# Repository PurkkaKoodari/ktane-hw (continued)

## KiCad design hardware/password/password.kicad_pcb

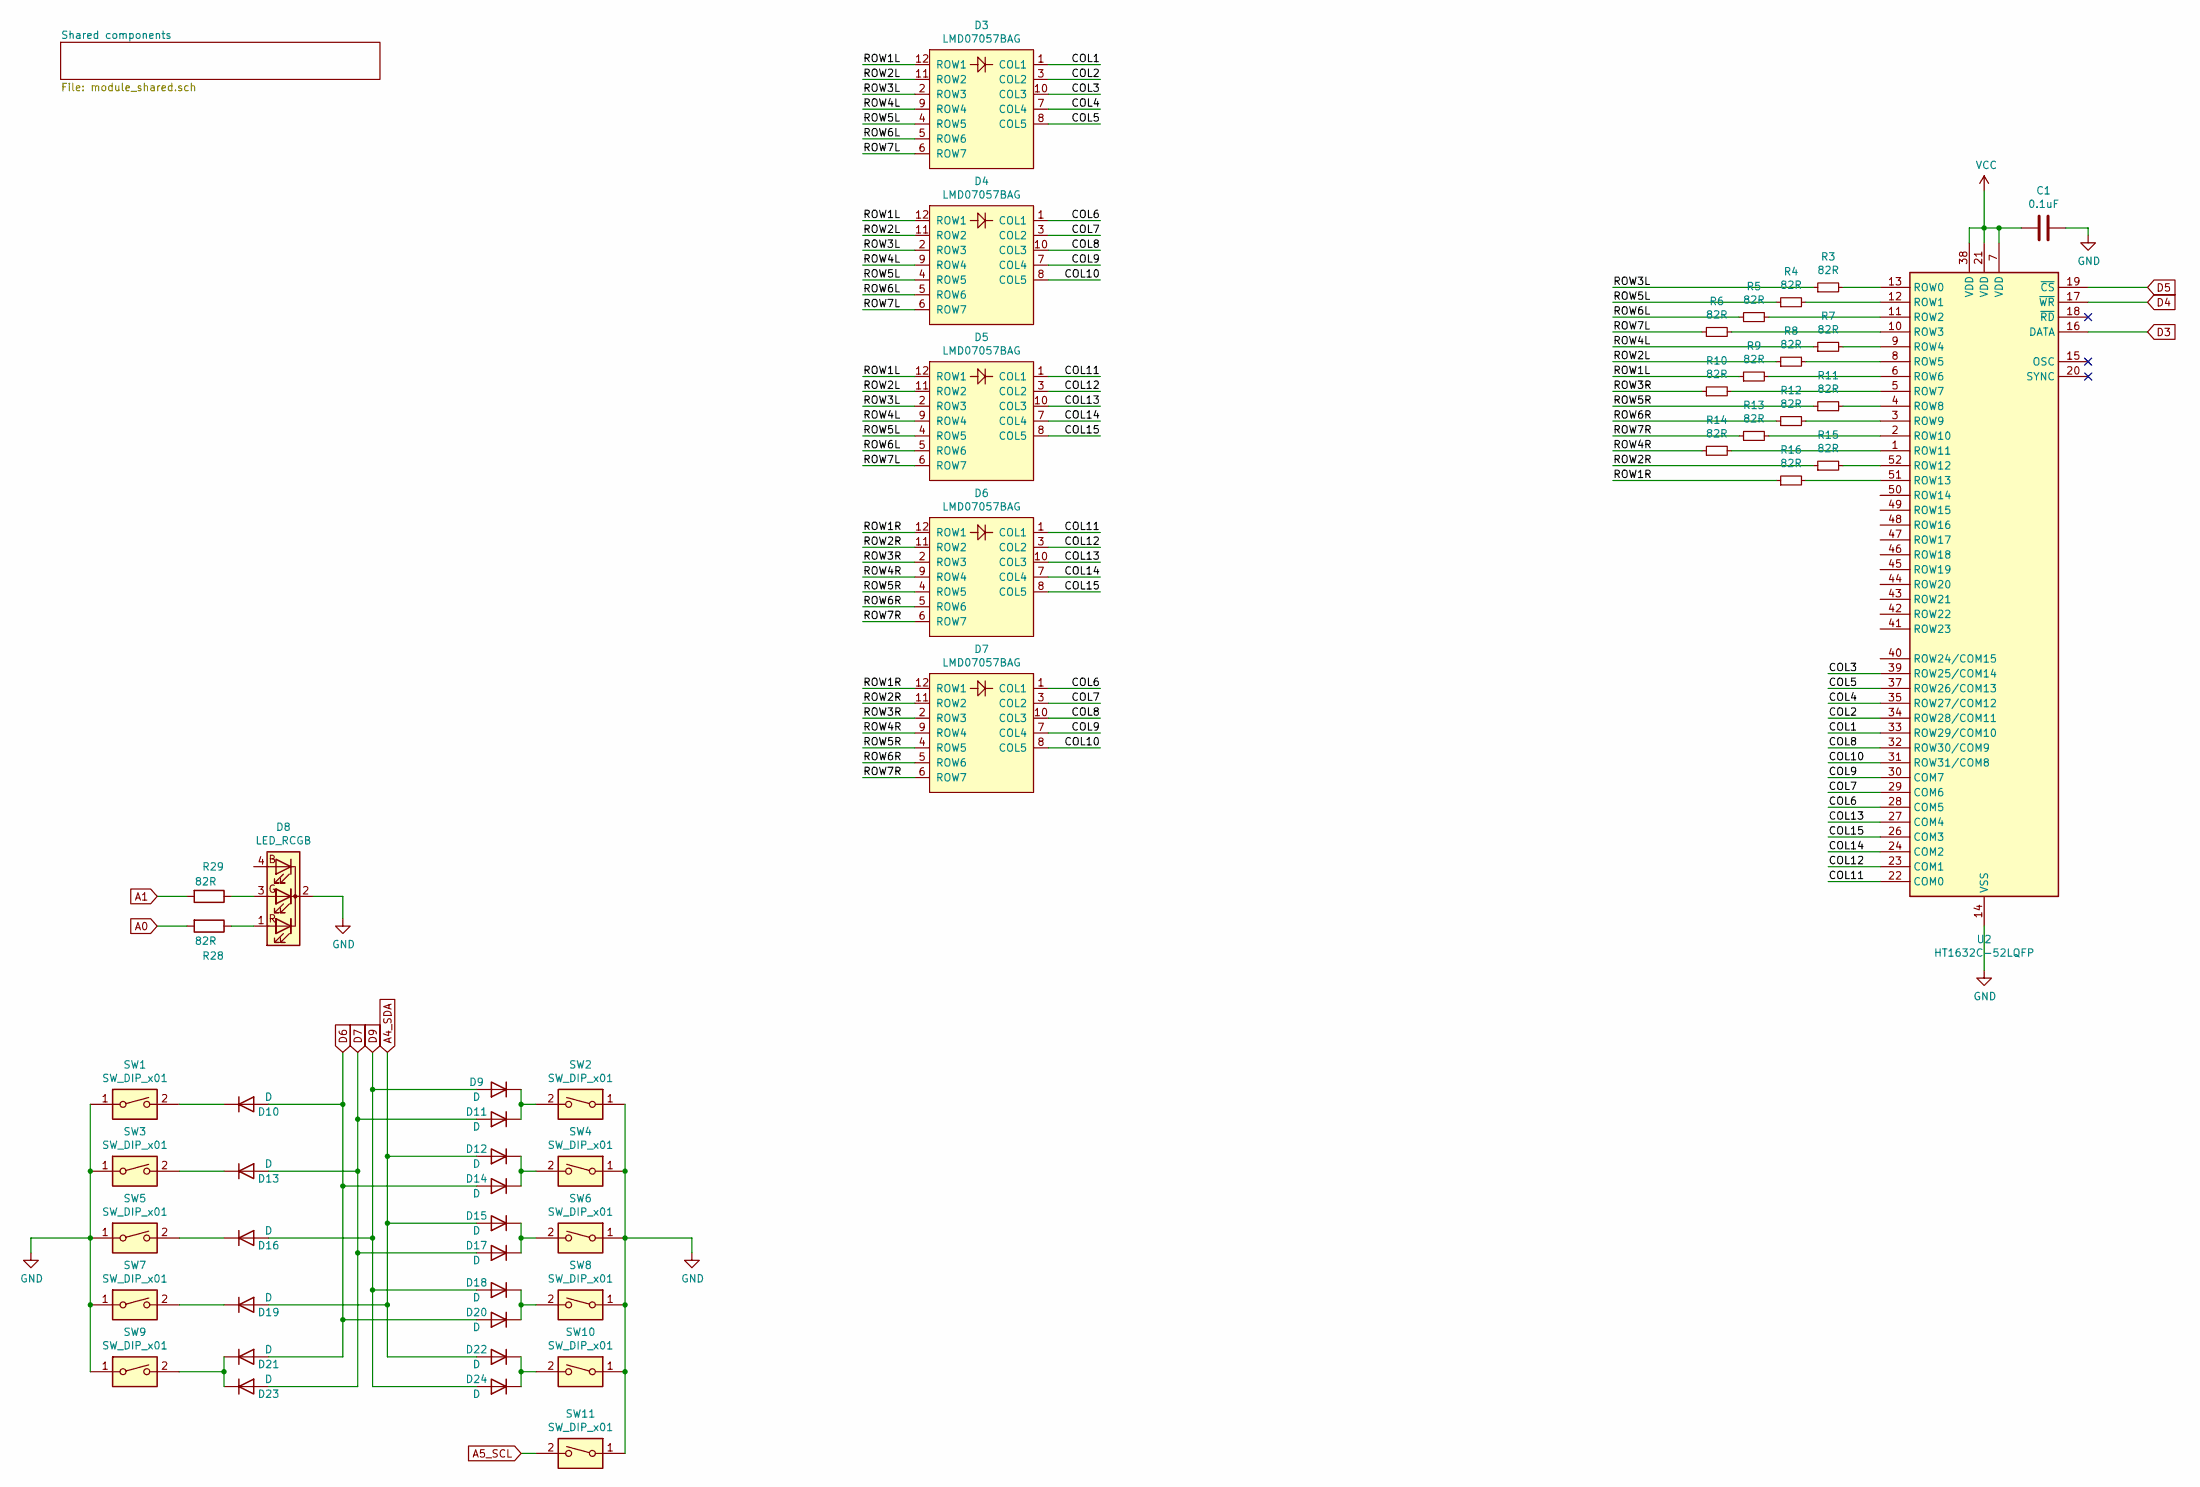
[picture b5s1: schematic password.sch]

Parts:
C1: 0.1uF; C_0603_1608Metric_Pad1.05x0.95mm_HandSolder
D3, D4, D5, D6, D7: LMD07057BAG
D8: LED_RCGB; LED_D5.0mm-4_RGB_Wide_Pins
D9, D10, D11, D12, D13, D14, D15, D16, D17, D18, D19, D20, D21, D22, D23, D24: D; D_0805_2012Metric_Pad1.15x1.40mm_HandSolder
R3, R4, R5, R6, R7, R8, R9, R10, R11, R12, R13, R14, R15, R16, R28, R29: 82R; R_0603_1608Metric_Pad0.98x0.95mm_HandSolder
SW1, SW2, SW3, SW4, SW5, SW6, SW7, SW8, SW9, SW10, SW11: SW_DIP_x01; SW_Push_1P1T_NO_6x6mm_H9.5mm
U2: HT1632C-52LQFP; LQFP-52_14x14mm_P1mm

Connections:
/COL1: D3.1 (COL1), U2.33 (ROW29/COM10)
/COL2: D3.3 (COL2), U2.34 (ROW28/COM11)
/COL3: D3.10 (COL3), U2.39 (ROW25/COM14)
/COL4: D3.7 (COL4), U2.35 (ROW27/COM12)
/COL5: D3.8 (COL5), U2.37 (ROW26/COM13)
/COL6: D4.1 (COL1), D7.1 (COL1), U2.28 (COM5)
/COL7: D4.3 (COL2), D7.3 (COL2), U2.29 (COM6)
/COL8: D4.10 (COL3), D7.10 (COL3), U2.32 (ROW30/COM9)
/COL9: D4.7 (COL4), D7.7 (COL4), U2.30 (COM7)
/COL10: D4.8 (COL5), D7.8 (COL5), U2.31 (ROW31/COM8)
/COL11: D5.1 (COL1), D6.1 (COL1), U2.22 (COM0)
/COL12: D5.3 (COL2), D6.3 (COL2), U2.23 (COM1)
/COL13: D5.10 (COL3), D6.10 (COL3), U2.27 (COM4)
/COL14: D5.7 (COL4), D6.7 (COL4), U2.24 (COM2)
/COL15: D5.8 (COL5), D6.8 (COL5), U2.26 (COM3)
/ROW1L: D3.12 (ROW1), D4.12 (ROW1), D5.12 (ROW1), R9.1
/ROW1R: D6.12 (ROW1), D7.12 (ROW1), R16.1
/ROW2L: D3.11 (ROW2), D4.11 (ROW2), D5.11 (ROW2), R8.1
/ROW2R: D6.11 (ROW2), D7.11 (ROW2), R15.1
/ROW3L: D3.2 (ROW3), D4.2 (ROW3), D5.2 (ROW3), R3.1
/ROW3R: D6.2 (ROW3), D7.2 (ROW3), R10.1
/ROW4L: D3.9 (ROW4), D4.9 (ROW4), D5.9 (ROW4), R7.1
/ROW4R: D6.9 (ROW4), D7.9 (ROW4), R14.1
/ROW5L: D3.4 (ROW5), D4.4 (ROW5), D5.4 (ROW5), R4.1
/ROW5R: D6.4 (ROW5), D7.4 (ROW5), R11.1
/ROW6L: D3.5 (ROW6), D4.5 (ROW6), D5.5 (ROW6), R5.1
/ROW6R: D6.5 (ROW6), D7.5 (ROW6), R12.1
/ROW7L: D3.6 (ROW7), D4.6 (ROW7), D5.6 (ROW7), R6.1
/ROW7R: D6.6 (ROW7), D7.6 (ROW7), R13.1
A0: R28.2; also elsewhere on the board
A1: R29.2; also elsewhere on the board
A4_SDA: D12.2 (A), D15.2 (A), D19.2 (A), D22.2 (A); also elsewhere on the board
A5_SCL: SW11.2; also elsewhere on the board
D3: U2.16 (DATA); also elsewhere on the board
D4: U2.17 (~WR); also elsewhere on the board
D5: U2.19 (~CS); also elsewhere on the board
D6: D10.2 (A), D14.2 (A), D20.2 (A), D21.2 (A); also elsewhere on the board
D7: D11.2 (A), D13.2 (A), D17.2 (A), D23.2 (A); also elsewhere on the board
D9: D9.2 (A), D16.2 (A), D18.2 (A), D24.2 (A); also elsewhere on the board
GND: C1.1, D8.2 (K), SW1.1, SW2.1, SW3.1, SW4.1, SW5.1, SW6.1, SW7.1, SW8.1, SW9.1, SW10.1, SW11.1, U2.14 (VSS), U2.25 (VSS), U2.36 (VSS); also elsewhere on the board
unnamed: D8.1 (RA), R28.1
unnamed: D8.3 (GA), R29.1
unnamed: D10.1 (K), SW1.2
unnamed: D9.1 (K), D11.1 (K), SW2.2
unnamed: D12.1 (K), D14.1 (K), SW4.2
unnamed: D13.1 (K), SW3.2
unnamed: D15.1 (K), D17.1 (K), SW6.2
unnamed: D16.1 (K), SW5.2
unnamed: D18.1 (K), D20.1 (K), SW8.2
unnamed: D19.1 (K), SW7.2
unnamed: D21.1 (K), D23.1 (K), SW9.2
unnamed: D22.1 (K), D24.1 (K), SW10.2
unnamed: R3.2, U2.13 (ROW0)
unnamed: R4.2, U2.12 (ROW1)
unnamed: R5.2, U2.11 (ROW2)
unnamed: R6.2, U2.10 (ROW3)
unnamed: R7.2, U2.9 (ROW4)
unnamed: R8.2, U2.8 (ROW5)
unnamed: R9.2, U2.6 (ROW6)
unnamed: R10.2, U2.5 (ROW7)
unnamed: R11.2, U2.4 (ROW8)
unnamed: R12.2, U2.3 (ROW9)
unnamed: R13.2, U2.2 (ROW10)
unnamed: R14.2, U2.1 (ROW11)
unnamed: R15.2, U2.52 (ROW12)
unnamed: R16.2, U2.51 (ROW13)
VCC: C1.2, U2.7 (VDD), U2.21 (VDD), U2.38 (VDD); also elsewhere on the board

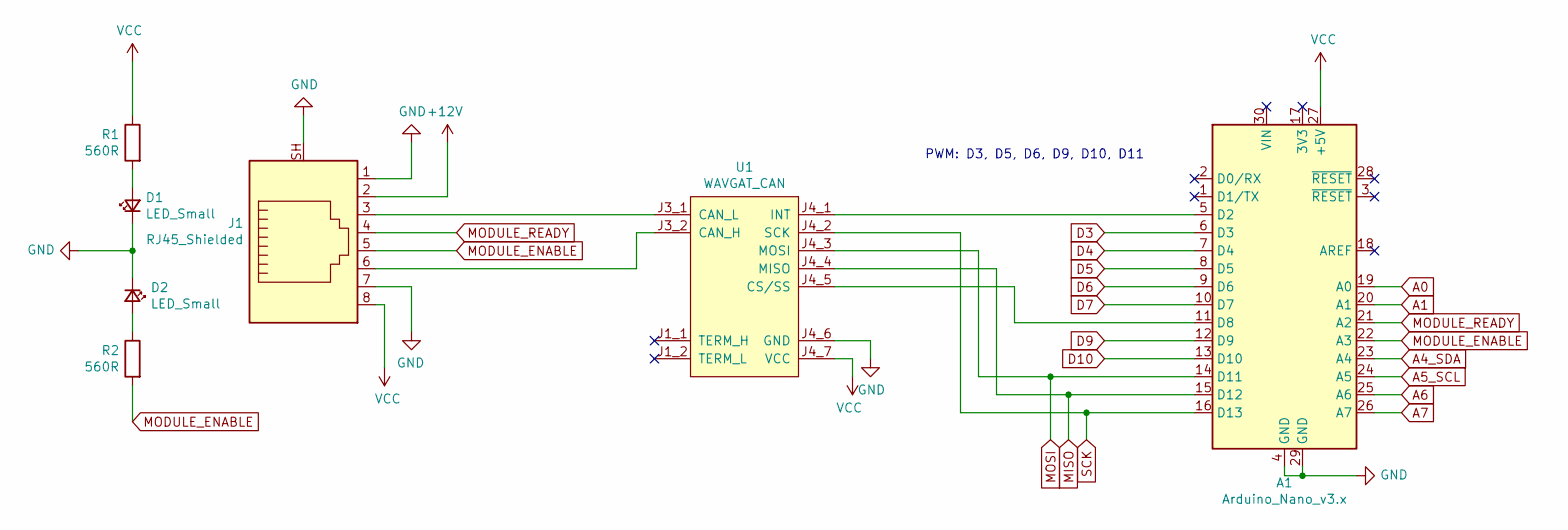
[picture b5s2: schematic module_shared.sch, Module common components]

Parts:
A1: Arduino_Nano_v3.x; Arduino_Nano
D1, D2: LED_Small; LED_D3.0mm
J1: RJ45_Shielded; RJ45_5224
R1, R2: 560R; R_0603_1608Metric_Pad0.98x0.95mm_HandSolder
U1: WAVGAT_CAN

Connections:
+12V: J1.2
A0: A1.19 (A0); also elsewhere on the board
A1: A1.20 (A1); also elsewhere on the board
A4_SDA: A1.23 (A4); also elsewhere on the board
A5_SCL: A1.24 (A5); also elsewhere on the board
A6: A1.25 (A6)
A7: A1.26 (A7)
D3: A1.6 (D3); also elsewhere on the board
D4: A1.7 (D4); also elsewhere on the board
D5: A1.8 (D5); also elsewhere on the board
D6: A1.9 (D6); also elsewhere on the board
D7: A1.10 (D7); also elsewhere on the board
D9: A1.12 (D9); also elsewhere on the board
D10: A1.13 (D10)
GND: A1.4 (GND), A1.29 (GND), D1.1 (K), D2.1 (K), J1.1, J1.7, J1.SH, U1.J4_6 (GND); also elsewhere on the board
MISO: A1.15 (D12), U1.J4_4 (MISO)
MODULE_ENABLE: A1.22 (A3), J1.5, R2.2
MODULE_READY: A1.21 (A2), J1.4
MOSI: A1.14 (D11), U1.J4_3 (MOSI)
unnamed: A1.5 (D2), U1.J4_1 (INT)
unnamed: A1.11 (D8), U1.J4_5 (CS/SS)
unnamed: D1.2 (A), R1.2
unnamed: D2.2 (A), R2.1
unnamed: J1.3, U1.J3_1 (CAN_L)
unnamed: J1.6, U1.J3_2 (CAN_H)
SCK: A1.16 (D13), U1.J4_2 (SCK)
VCC: A1.27 (+5V), J1.8, R1.1, U1.J4_7 (VCC); also elsewhere on the board

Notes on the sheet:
PWM: D3, D5, D6, D9, D10, D11

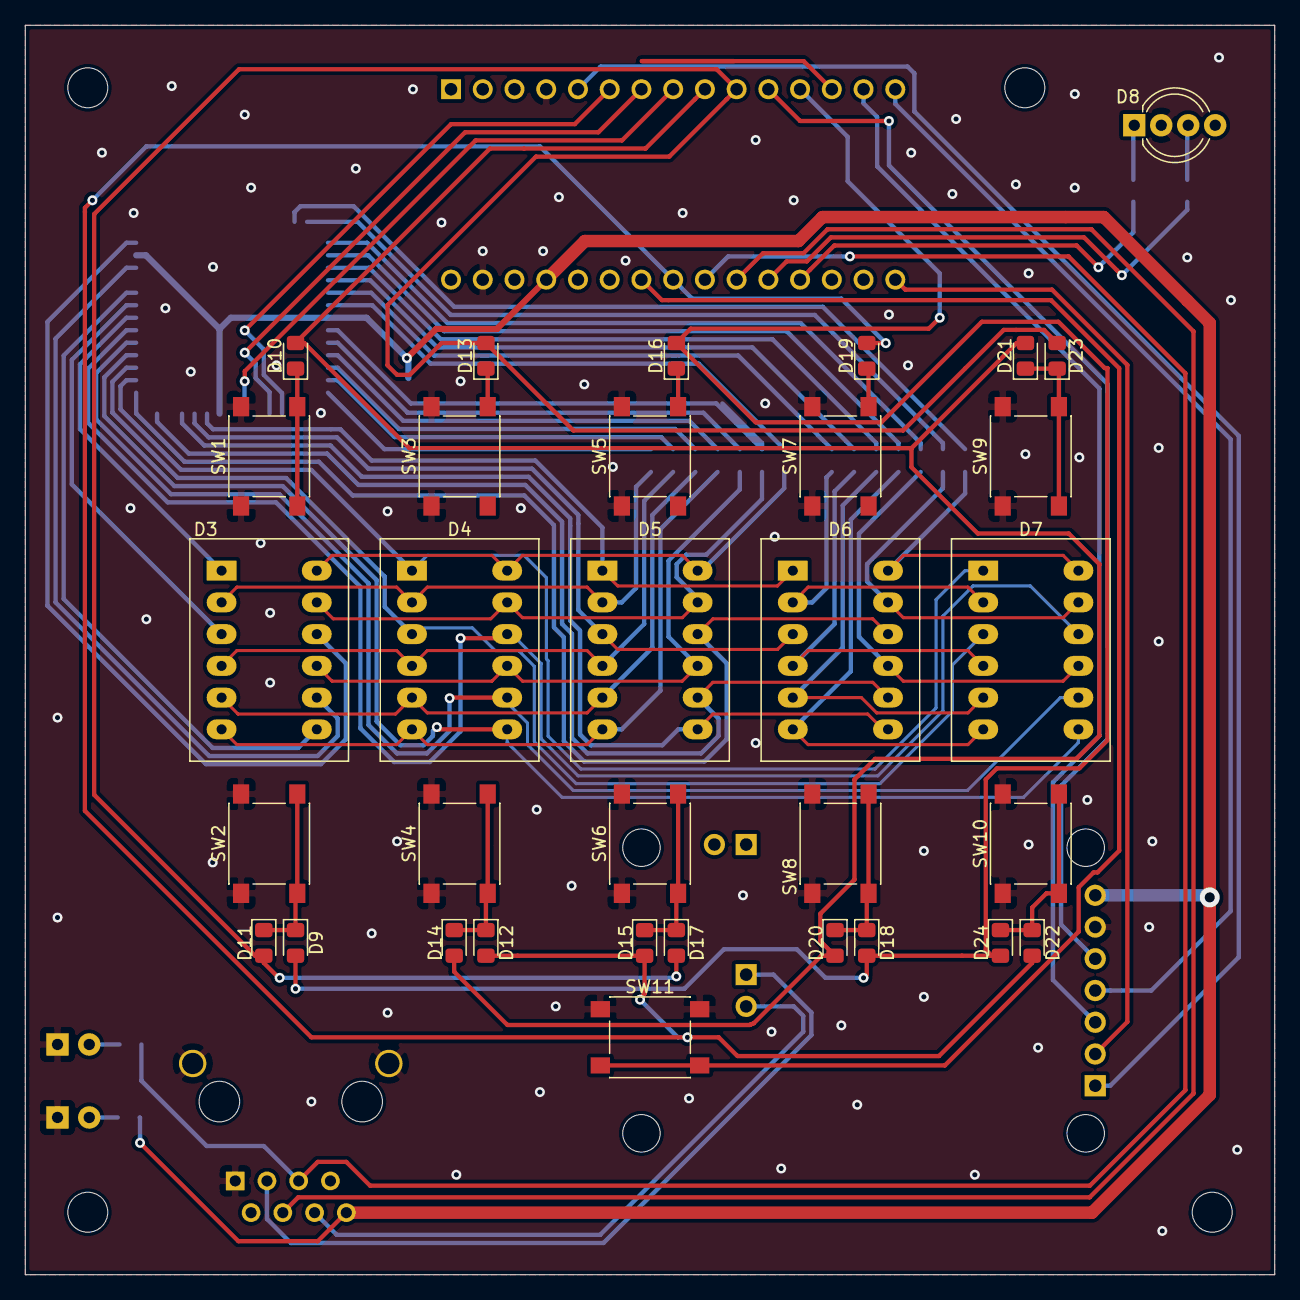
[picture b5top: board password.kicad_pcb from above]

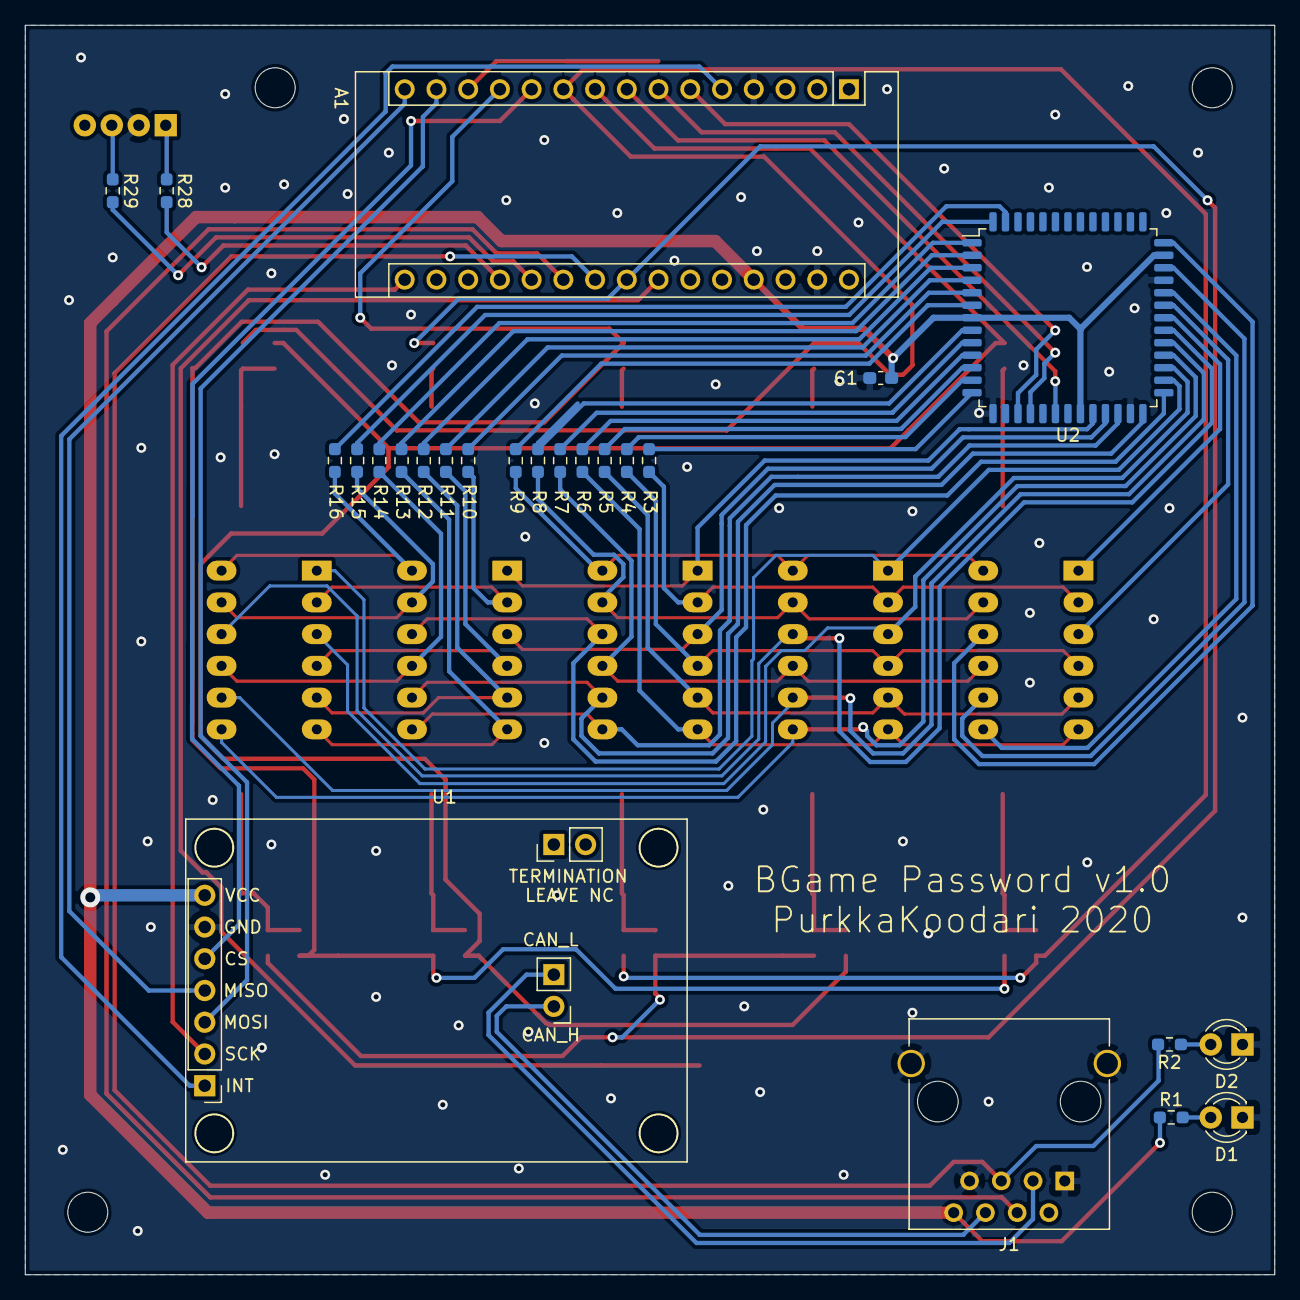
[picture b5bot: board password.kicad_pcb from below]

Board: 2 copper layers, 100.0 x 100.0 mm, 58 parts (25 on the bottom side), 78 nets.

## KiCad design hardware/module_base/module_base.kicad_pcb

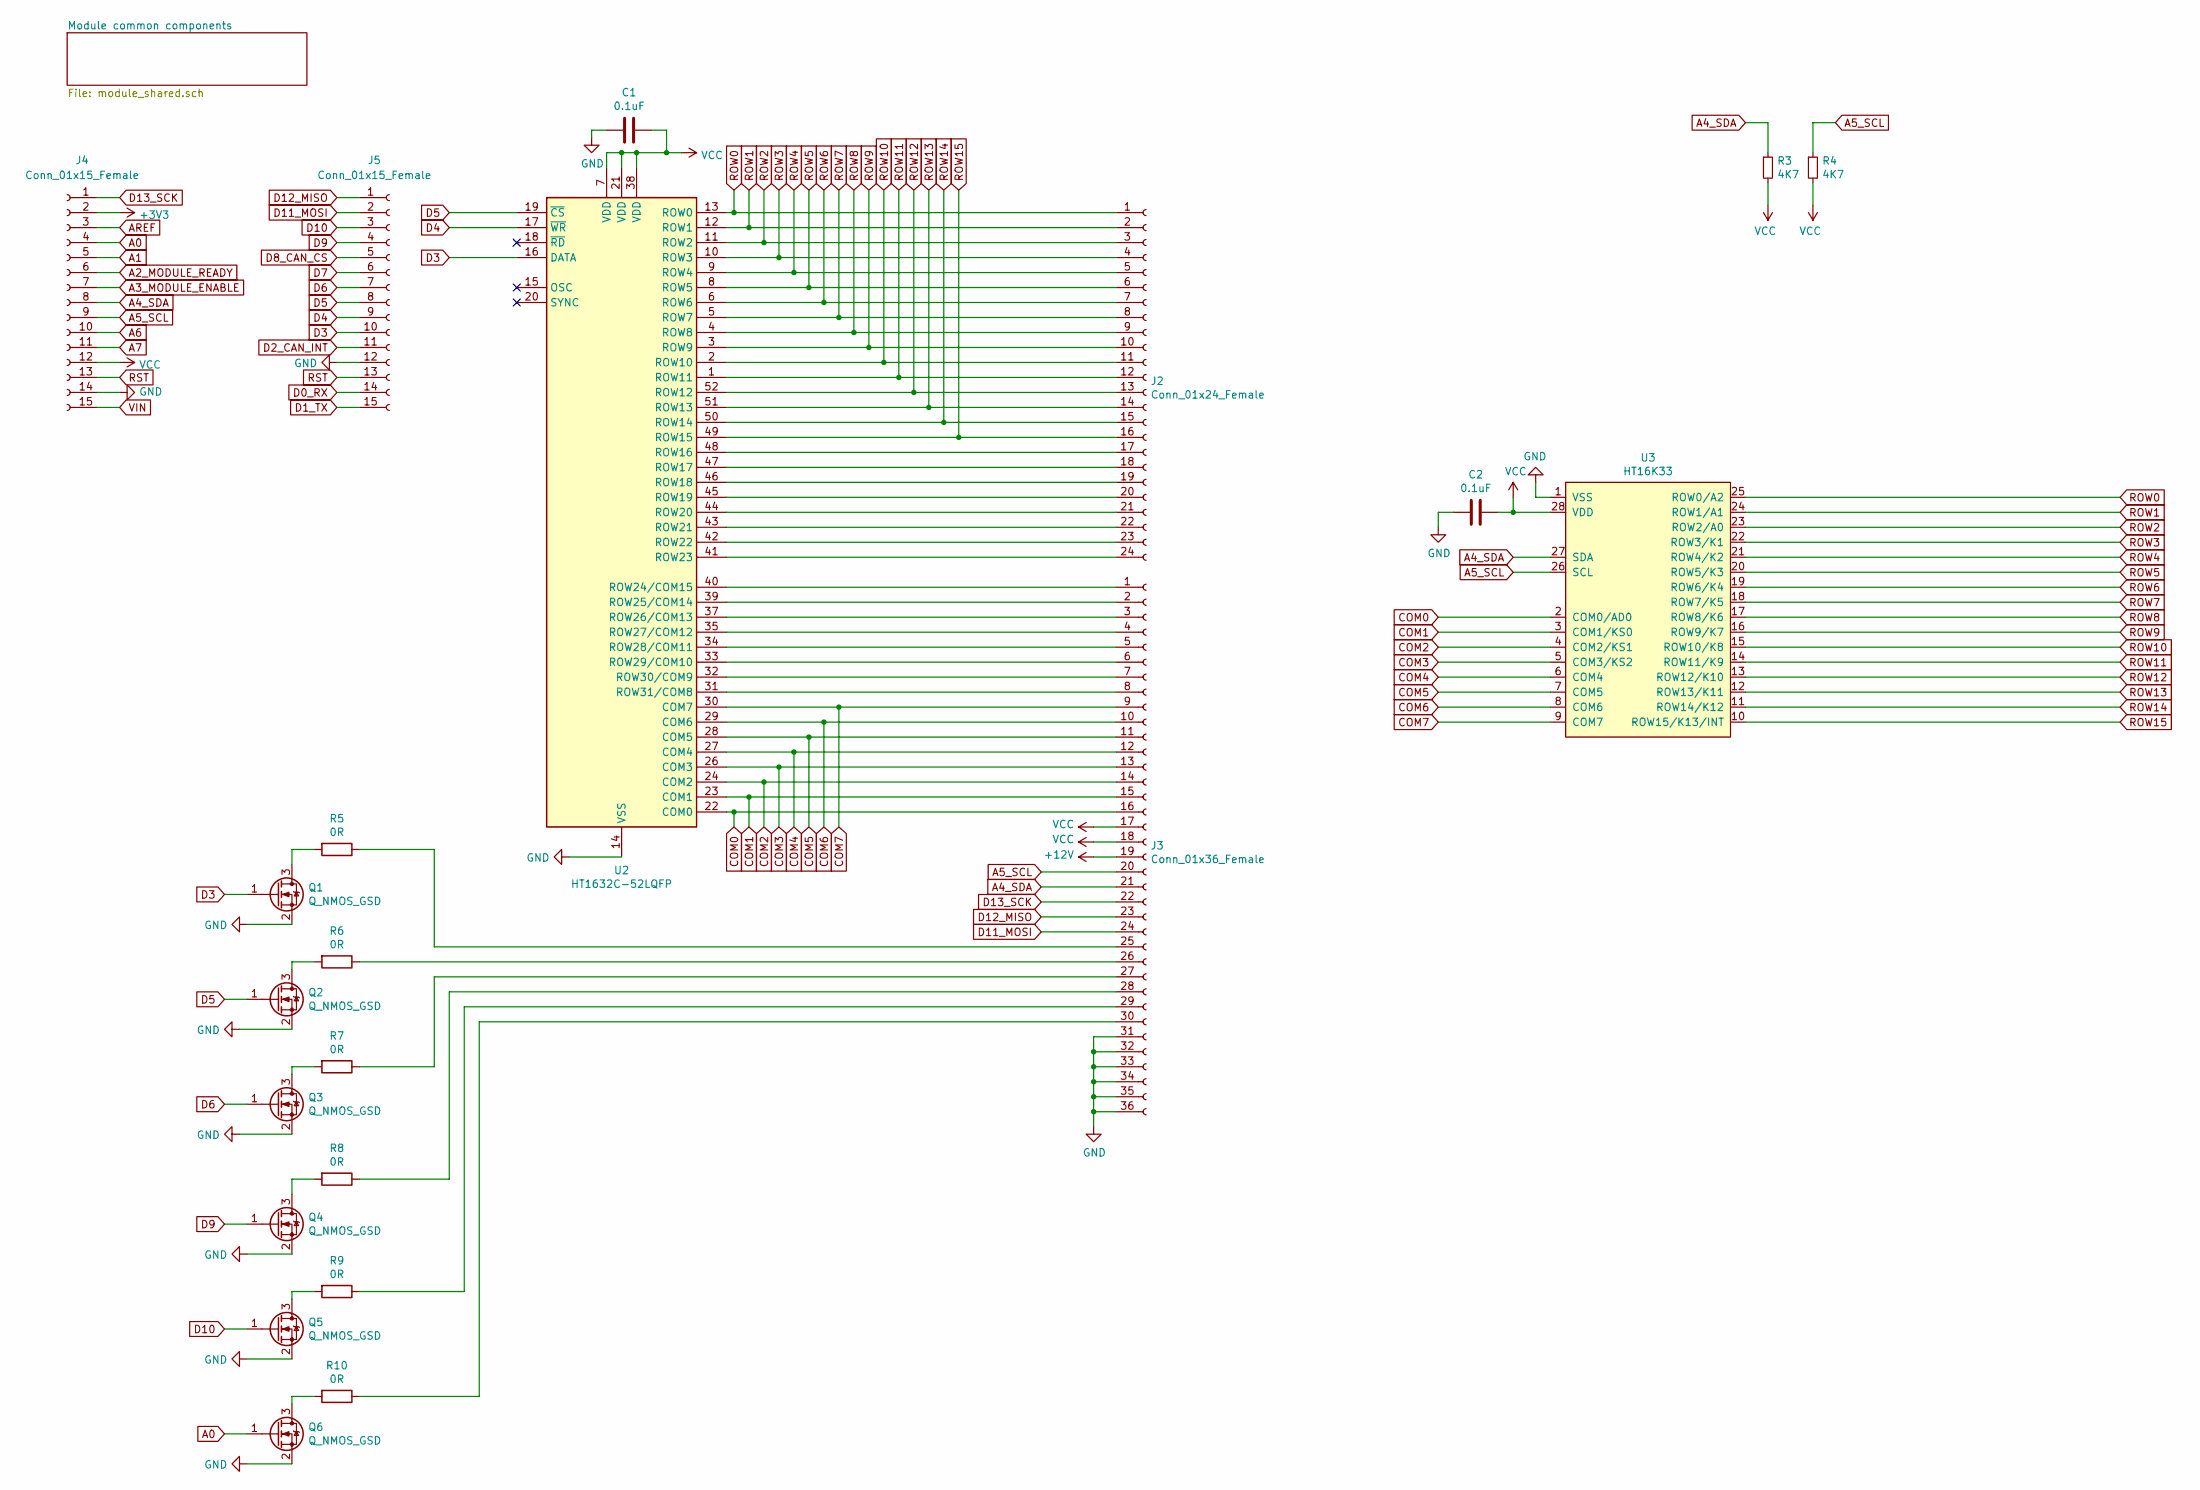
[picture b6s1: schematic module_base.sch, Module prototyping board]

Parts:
C1, C2: 0.1uF; C_0603_1608Metric_Pad1.08x0.95mm_HandSolder
J2: Conn_01x24_Female; PinSocket_1x24_P2.54mm_Vertical
J3: Conn_01x36_Female; PinSocket_1x36_P2.54mm_Vertical
J4, J5: Conn_01x15_Female; PinSocket_1x15_P2.54mm_Vertical
Q1, Q2, Q3, Q4, Q5, Q6: Q_NMOS_GSD; SOT-23_Handsoldering
R3, R4: 4K7; R_0603_1608Metric_Pad0.98x0.95mm_HandSolder
R5, R6, R7, R8, R9, R10: 0R; R_0603_1608Metric_Pad0.98x0.95mm_HandSolder
U2: HT1632C-52LQFP; QFP-52_14x14_Pitch1mm_HandSoldering
U3: HT16K33; SOIC-28W_7.5x17.9mm_P1.27mm

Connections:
+3V3: J4.2; also elsewhere on the board
+12V: J3.19; also elsewhere on the board
A0: J4.4, Q6.1 (G); also elsewhere on the board
A1: J4.5; also elsewhere on the board
A2_MODULE_READY: J4.6; also elsewhere on the board
A3_MODULE_ENABLE: J4.7; also elsewhere on the board
A4_SDA: J3.21, J4.8, R3.1, U3.27 (SDA); also elsewhere on the board
A5_SCL: J3.20, J4.9, R4.1, U3.26 (SCL); also elsewhere on the board
A6: J4.10; also elsewhere on the board
A7: J4.11; also elsewhere on the board
AREF: J4.3; also elsewhere on the board
COM0: J3.16, U2.22 (COM0), U3.2 (COM0/AD0)
COM1: J3.15, U2.23 (COM1), U3.3 (COM1/KS0)
COM2: J3.14, U2.24 (COM2), U3.4 (COM2/KS1)
COM3: J3.13, U2.26 (COM3), U3.5 (COM3/KS2)
COM4: J3.12, U2.27 (COM4), U3.6 (COM4)
COM5: J3.11, U2.28 (COM5), U3.7 (COM5)
COM6: J3.10, U2.29 (COM6), U3.8 (COM6)
COM7: J3.9, U2.30 (COM7), U3.9 (COM7)
D0_RX: J5.14; also elsewhere on the board
D1_TX: J5.15; also elsewhere on the board
D2_CAN_INT: J5.11; also elsewhere on the board
D3: J5.10, Q1.1 (G), U2.16 (DATA); also elsewhere on the board
D4: J5.9, U2.17 (~WR); also elsewhere on the board
D5: J5.8, Q2.1 (G), U2.19 (~CS); also elsewhere on the board
D6: J5.7, Q3.1 (G); also elsewhere on the board
D7: J5.6; also elsewhere on the board
D8_CAN_CS: J5.5; also elsewhere on the board
D9: J5.4, Q4.1 (G); also elsewhere on the board
D10: J5.3, Q5.1 (G); also elsewhere on the board
D11_MOSI: J3.24, J5.2; also elsewhere on the board
D12_MISO: J3.23, J5.1; also elsewhere on the board
D13_SCK: J3.22, J4.1; also elsewhere on the board
GND: C1.2, C2.2, J3.31, J3.32, J3.33, J3.34, J3.35, J3.36, J4.14, J5.12, Q1.2 (S), Q2.2 (S), Q3.2 (S), Q4.2 (S), Q5.2 (S), Q6.2 (S), U2.14 (VSS), U2.25 (VSS), U2.36 (VSS), U3.1 (VSS); also elsewhere on the board
unnamed: J2.17, U2.48 (ROW16)
unnamed: J2.18, U2.47 (ROW17)
unnamed: J2.19, U2.46 (ROW18)
unnamed: J2.20, U2.45 (ROW19)
unnamed: J2.21, U2.44 (ROW20)
unnamed: J2.22, U2.43 (ROW21)
unnamed: J2.23, U2.42 (ROW22)
unnamed: J2.24, U2.41 (ROW23)
unnamed: J3.1, U2.40 (ROW24/COM15)
unnamed: J3.2, U2.39 (ROW25/COM14)
unnamed: J3.3, U2.37 (ROW26/COM13)
unnamed: J3.4, U2.35 (ROW27/COM12)
unnamed: J3.5, U2.34 (ROW28/COM11)
unnamed: J3.6, U2.33 (ROW29/COM10)
unnamed: J3.7, U2.32 (ROW30/COM9)
unnamed: J3.8, U2.31 (ROW31/COM8)
unnamed: J3.25, R5.1
unnamed: J3.26, R6.1
unnamed: J3.27, R7.1
unnamed: J3.28, R8.1
unnamed: J3.29, R9.1
unnamed: J3.30, R10.1
unnamed: Q1.3 (D), R5.2
unnamed: Q2.3 (D), R6.2
unnamed: Q3.3 (D), R7.2
unnamed: Q4.3 (D), R8.2
unnamed: Q5.3 (D), R9.2
unnamed: Q6.3 (D), R10.2
ROW0: J2.1, U2.13 (ROW0), U3.25 (ROW0/A2)
ROW1: J2.2, U2.12 (ROW1), U3.24 (ROW1/A1)
ROW2: J2.3, U2.11 (ROW2), U3.23 (ROW2/A0)
ROW3: J2.4, U2.10 (ROW3), U3.22 (ROW3/K1)
ROW4: J2.5, U2.9 (ROW4), U3.21 (ROW4/K2)
ROW5: J2.6, U2.8 (ROW5), U3.20 (ROW5/K3)
ROW6: J2.7, U2.6 (ROW6), U3.19 (ROW6/K4)
ROW7: J2.8, U2.5 (ROW7), U3.18 (ROW7/K5)
ROW8: J2.9, U2.4 (ROW8), U3.17 (ROW8/K6)
ROW9: J2.10, U2.3 (ROW9), U3.16 (ROW9/K7)
ROW10: J2.11, U2.2 (ROW10), U3.15 (ROW10/K8)
ROW11: J2.12, U2.1 (ROW11), U3.14 (ROW11/K9)
ROW12: J2.13, U2.52 (ROW12), U3.13 (ROW12/K10)
ROW13: J2.14, U2.51 (ROW13), U3.12 (ROW13/K11)
ROW14: J2.15, U2.50 (ROW14), U3.11 (ROW14/K12)
ROW15: J2.16, U2.49 (ROW15), U3.10 (ROW15/K13/INT)
RST: J4.13, J5.13; also elsewhere on the board
VCC: C1.1, C2.1, J3.17, J3.18, J4.12, R3.2, R4.2, U2.7 (VDD), U2.21 (VDD), U2.38 (VDD), U3.28 (VDD); also elsewhere on the board
VIN: J4.15; also elsewhere on the board

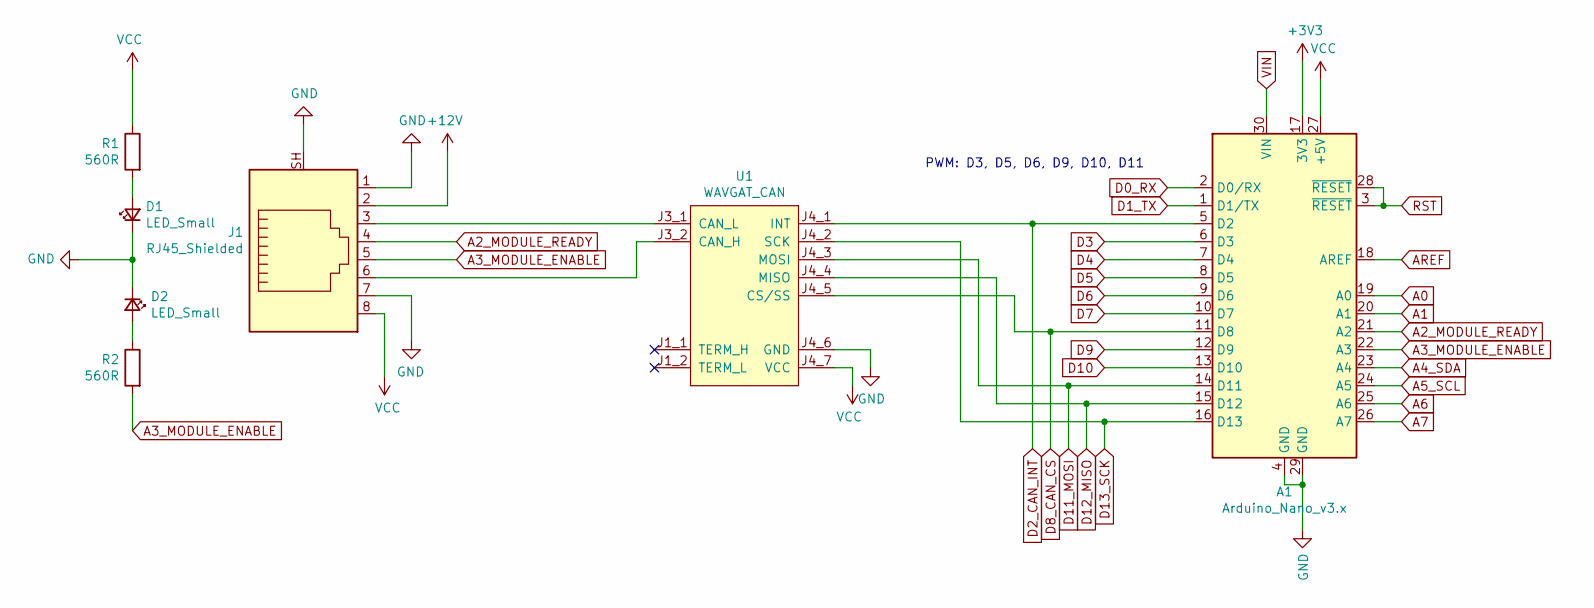
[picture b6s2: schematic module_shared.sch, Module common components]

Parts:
A1: Arduino_Nano_v3.x; Arduino_Nano
D1, D2: LED_Small; LED_D3.0mm
J1: RJ45_Shielded; RJ45_5224
R1, R2: 560R; R_0603_1608Metric_Pad0.98x0.95mm_HandSolder
U1: WAVGAT_CAN

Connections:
+3V3: A1.17 (3V3); also elsewhere on the board
+12V: J1.2; also elsewhere on the board
A0: A1.19 (A0); also elsewhere on the board
A1: A1.20 (A1); also elsewhere on the board
A2_MODULE_READY: A1.21 (A2), J1.4; also elsewhere on the board
A3_MODULE_ENABLE: A1.22 (A3), J1.5, R2.2; also elsewhere on the board
A4_SDA: A1.23 (A4); also elsewhere on the board
A5_SCL: A1.24 (A5); also elsewhere on the board
A6: A1.25 (A6); also elsewhere on the board
A7: A1.26 (A7); also elsewhere on the board
AREF: A1.18 (AREF); also elsewhere on the board
D0_RX: A1.2 (D0/RX); also elsewhere on the board
D1_TX: A1.1 (D1/TX); also elsewhere on the board
D2_CAN_INT: A1.5 (D2), U1.J4_1 (INT); also elsewhere on the board
D3: A1.6 (D3); also elsewhere on the board
D4: A1.7 (D4); also elsewhere on the board
D5: A1.8 (D5); also elsewhere on the board
D6: A1.9 (D6); also elsewhere on the board
D7: A1.10 (D7); also elsewhere on the board
D8_CAN_CS: A1.11 (D8), U1.J4_5 (CS/SS); also elsewhere on the board
D9: A1.12 (D9); also elsewhere on the board
D10: A1.13 (D10); also elsewhere on the board
D11_MOSI: A1.14 (D11), U1.J4_3 (MOSI); also elsewhere on the board
D12_MISO: A1.15 (D12), U1.J4_4 (MISO); also elsewhere on the board
D13_SCK: A1.16 (D13), U1.J4_2 (SCK); also elsewhere on the board
GND: A1.4 (GND), A1.29 (GND), D1.1 (K), D2.1 (K), J1.1, J1.7, J1.SH, U1.J4_6 (GND); also elsewhere on the board
unnamed: D1.2 (A), R1.2
unnamed: D2.2 (A), R2.1
unnamed: J1.3, U1.J3_1 (CAN_L)
unnamed: J1.6, U1.J3_2 (CAN_H)
RST: A1.3 (~RESET), A1.28 (~RESET); also elsewhere on the board
VCC: A1.27 (+5V), J1.8, R1.1, U1.J4_7 (VCC); also elsewhere on the board
VIN: A1.30 (VIN); also elsewhere on the board

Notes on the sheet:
PWM: D3, D5, D6, D9, D10, D11

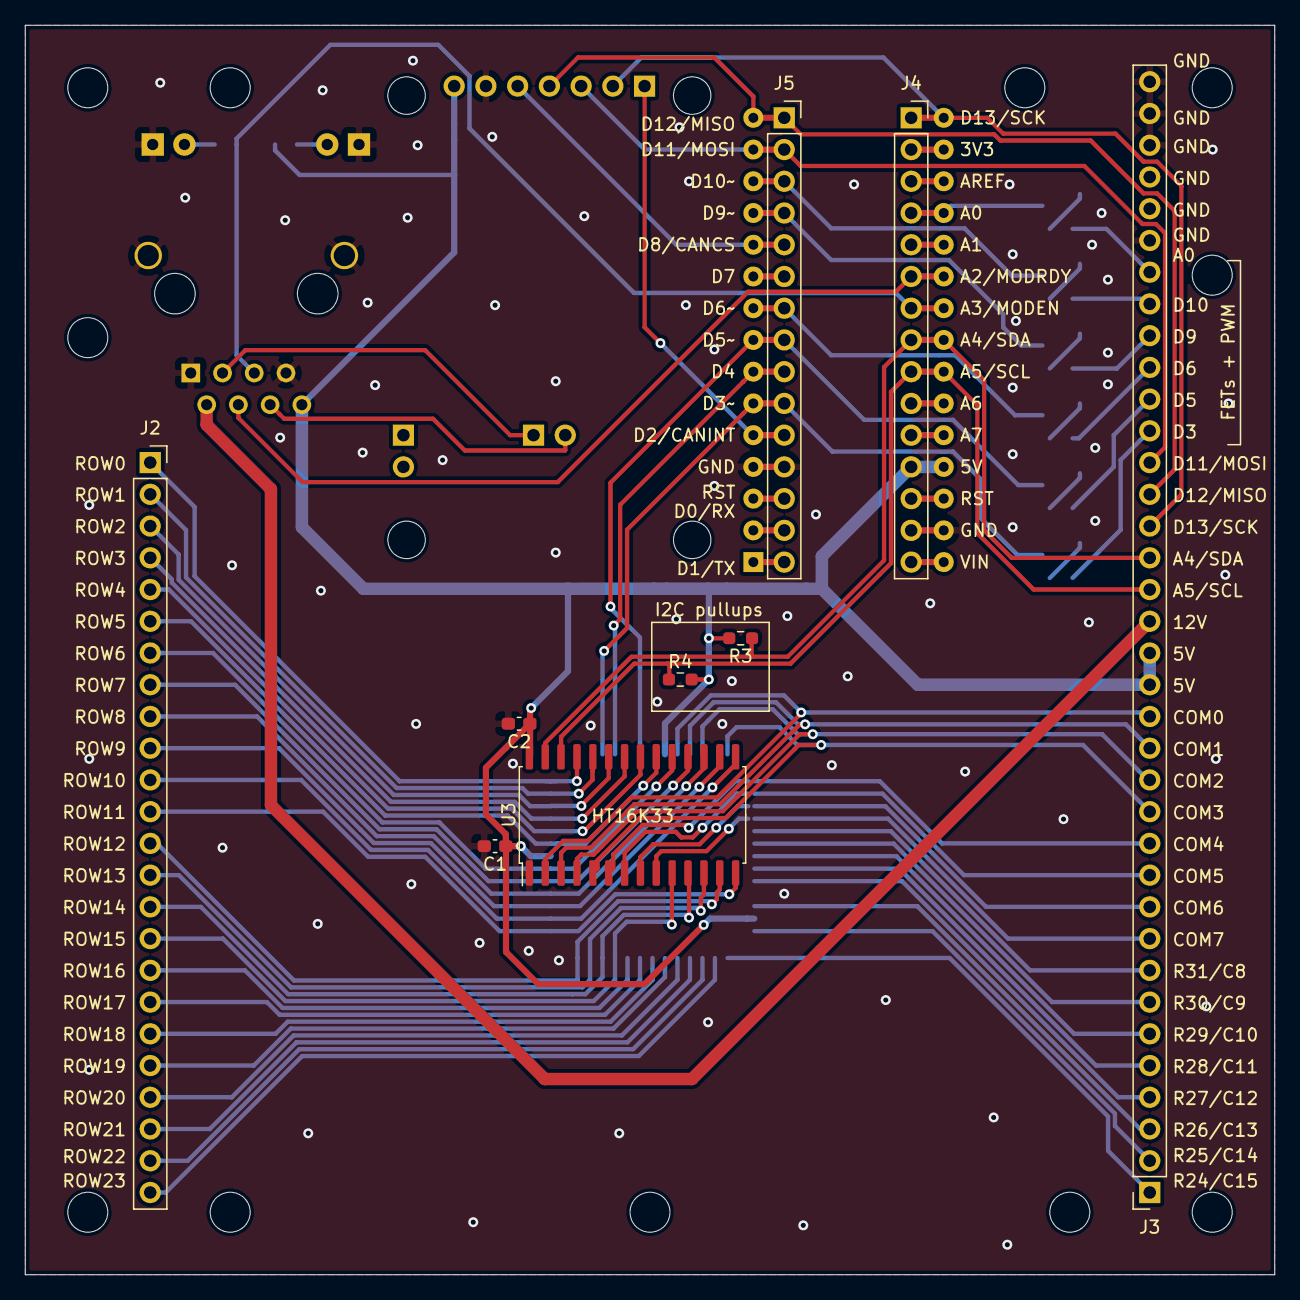
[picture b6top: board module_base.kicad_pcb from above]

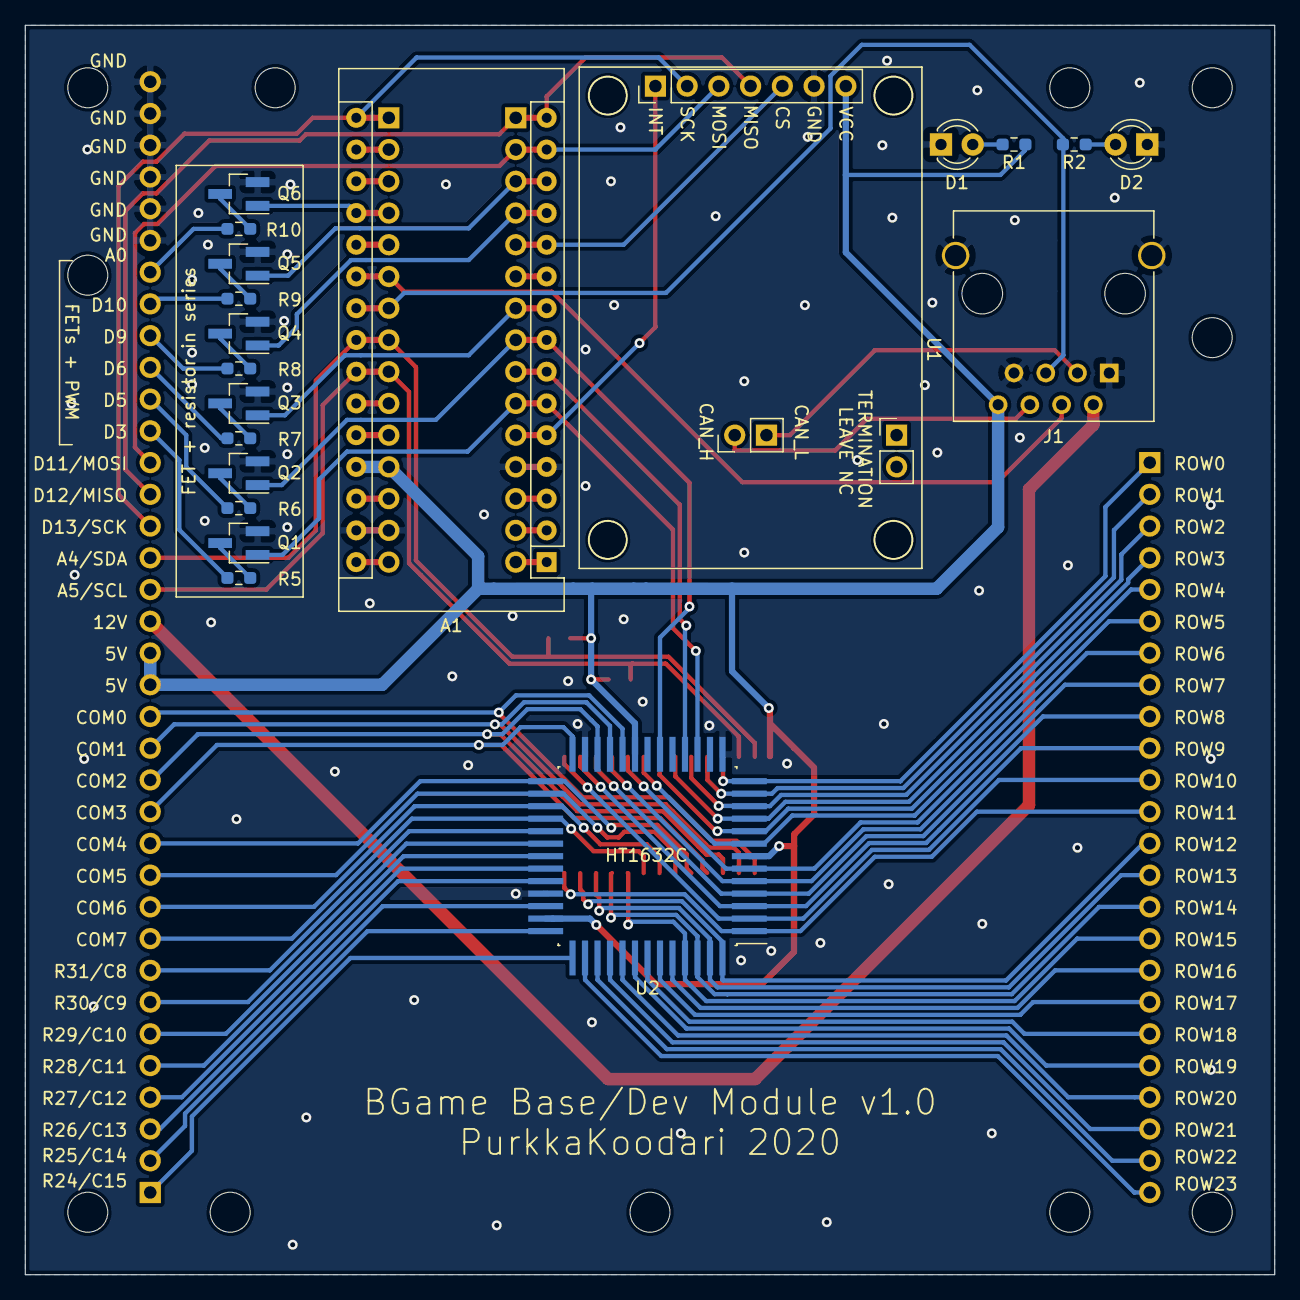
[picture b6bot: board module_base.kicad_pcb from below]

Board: 2 copper layers, 100.0 x 100.0 mm, 29 parts (20 on the bottom side), 85 nets.
